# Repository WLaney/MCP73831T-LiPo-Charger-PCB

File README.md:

# MCP73831T-LiPo-Charger-PCB

This is a breakout board for the MCP73831T IC. The MCP73831T is a LiPo charging chip.

This board was desgined as part of the Sharkduino Project at The College of William and Mary, more information can be found at [sharkduino.com](http://www.sharkduino.com)

## License Information

This hardware is released under [Creative Commons ShareAlike 4.0 International](https://creativecommons.org/licenses/by-sa/4.0/).

It is derived from the [SparkFun LiPo Charger Basic](https://github.com/sparkfun/Lipo_Charger_Basic-microUSB/tree/V_1.0), desgined by SparkFun Electronics.

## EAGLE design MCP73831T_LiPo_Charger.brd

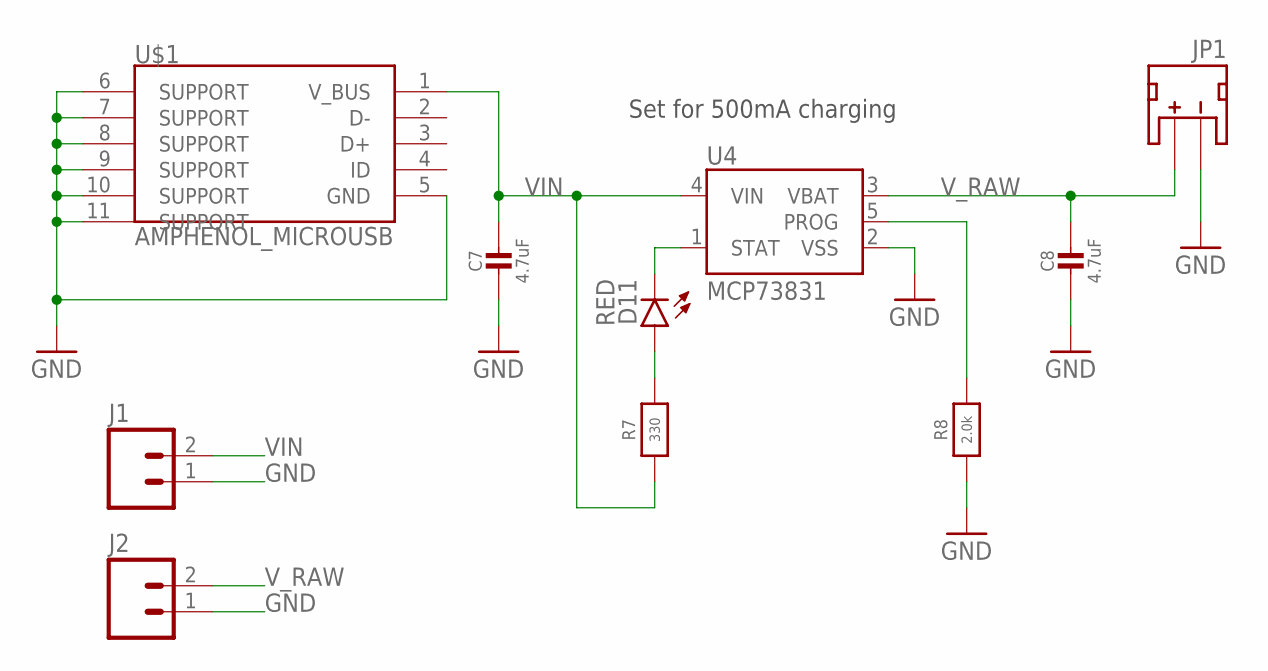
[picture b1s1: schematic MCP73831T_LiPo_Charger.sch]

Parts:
C7, C8: 4.7uF; 0805-NO
D11: RED; LED-0603
J1, J2: M02PTH; 1X02
JP1: JST; JST-2-SMD@1
R7: 330; _0805MP
R8: 2.0k; _0805MP
U4: MCP73831; SOT23-5
U$1: AMPHENOL_MICROUSB

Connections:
GND: C7.2, C8.2, J1.1, J2.1, JP1.1 (-), R8.1, U4.2 (VSS), U$1.5 (GND), U$1.6 (SUPPORT), U$1.7 (SUPPORT), U$1.8 (SUPPORT), U$1.9 (SUPPORT), U$1.10 (SUPPORT), U$1.11 (SUPPORT)
unnamed: D11.A, R7.2
PROG: R8.2, U4.5 (PROG)
STAT: D11.C, U4.1 (STAT)
VIN: C7.1, J1.2, R7.1, U4.4 (VIN), U$1.1 (V_BUS)
V_RAW: C8.1, J2.2, JP1.2 (+), U4.3 (VBAT)

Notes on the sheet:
Set for 500mA charging

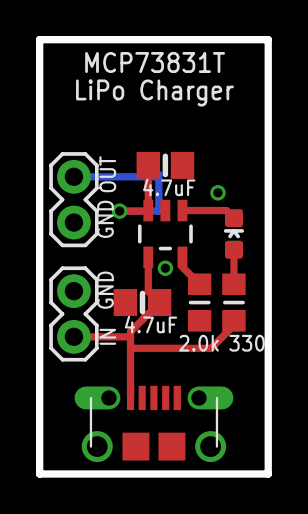
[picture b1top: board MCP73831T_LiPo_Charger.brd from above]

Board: 2 copper layers, 12.7 x 24.1 mm, 10 parts (1 on the bottom side), 6 nets.

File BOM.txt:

component/value, size, quanity, digikey part number
--------------------------------------------------------
MCP73831 IC, SC-74A/SOT-753, 1, MCP73831T-2ATI/OTCT-ND
JST Male, 2mm, 1, 455-1749-1-ND
USB micro SMD+TH, NA, 1, 609-4618-1-ND
4.7uF capacitor, 0805, 2, 490-3335-1-ND
330 resistor, 0805, 1, 311-330CRCT-ND
2k resistor, 0805, 1, 311-2.00KCRCT-ND
Red LED, 0603, 1, 754-1122-1-ND

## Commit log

2017-09-29 inital commit
2017-09-29 created schematic
    Moved charging circuit over from sharkduino V2.1
    Switched the uUSB port to the one used by adafruit on there [micro lipo charger](https://www.adafruit.com/product/1904)
2017-09-29 added headers to schematic
2017-09-30 inital layout
2017-09-30 added part silk lable
2017-09-30 put silk on tPlace
2017-09-30 finish silk
2017-10-01 silk updates
2017-10-01 created BOM
2017-10-01 silk changes for manufacturing
2017-10-02 increased via drill size to 0.02
    this puts the drill size in line with the sharkduino 2.x boards, and makes the
    sparkfun DRC happy
2017-10-24 updated BOM
2017-10-24 created desgin documentation
2017-11-30 modified microUSB port
2017-12-13 modified microusb port and lipo schematic
2017-12-15 final changes for osh park order

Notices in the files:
parts and their libraries:
SparkFun-LED: Licensing: Creative Commons ShareAlike 4.0 International - https://creativecommons.org/licenses/by-sa/4.0
